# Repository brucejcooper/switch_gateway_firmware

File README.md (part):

# Switch Gateway Lighting System

A complete home lighting control system built around a **WIZnet W5100S-EVB-Pico
(RP2040)** as the central controller. The board owns all physical hardware,
controls lights in response to button presses, and talks to Home Assistant via
MQTT **directly over its on-board Ethernet** — no external bridge host.

> **On-board MQTT (current architecture).** The MQTT bridge that once ran as an
> external `mqtt_bridge.py` process on a USB-tethered host now runs **on-board on
> Pico core 1**, over the W5100S hardwired TCP/IP chip. The Python bridge has
> been **deleted** — it lives only in git history as a behavioural reference for
> the C reimplementation in `src/net/`. As a consequence the USB-CDC port is now
> a **human text CLI only**: it carries no JSON command/event stream.

---

## System Architecture

```
RS-485 bus @ 38400 baud (canonical; firmware auto-recovers slaves left at 19200 or 9600)

W5100S-EVB-Pico (RP2040) — Modbus master, single source of truth
 ├── core 0: Modbus master · button matrix (PIO) · button FSM · DALI world
 │           model · command queue · state cache · persistence · USB-CDC CLI
 ├── core 1: W5100S Ethernet · MQTT connection mgmt · Home Assistant
 │           discovery / availability / state ↔ command translation (JSON)
 │
 ├── Waveshare 32CH Relay Board (slave 1)   — 32 relay coils
 ├── TinyModbus DALI Gateway (slave 2)      — up to 64 ballasts
 ├── TinyModbus DALI Gateway (slave 3)      — up to 64 ballasts
 └── 24 switch fixtures × up to 7 buttons   — PIO matrix scan

   │ Ethernet (W5100S, on-board)              │ USB CDC (human text CLI only)
   ▼                                          ▼
 Mosquitto + Home Assistant            screen / picocom / miniterm
```

The two cores exchange **typed C structs** over two single-producer/single-
consumer queues (`intercore.c`) — **not JSON**. Core 0 forwards state events to
core 1 (`ic_event_t`); core 1 forwards translated commands back to core 0
(`ic_cmd_t`). JSON exists only at core 1's MQTT edge (`src/net/ha_bridge.c`).

### Key design principles

**The board is the master.** It owns the RS-485 bus and all lighting state. HA is
a client — if HA, the broker, or the network goes away, buttons and lights keep
working normally. A network outage never reboots the device: core 1 keeps looping
through its reconnect state machine while core 0 runs the lights. Core 0 only
feeds the hardware watchdog while core 1's heartbeat is fresh, so a genuine
core-1 wedge (not a network outage) is what triggers a reboot.

**State is never assumed.** Core 0 only updates its state cache from hardware
readback — DALI queries sent to the ballasts themselves — never from the
commands it sent. The gateway caches nothing, so the ballasts are the only
authority.
This correctly handles DALI min/max level clamping and ballast-side fade curves.

**Discovery is republished on every connect.** On each MQTT (re)connect core 1
re-publishes the full HA auto-discovery set and then requests a `resync`, so HA
repopulates from scratch. Broker and network settings live in `/config.json`
(set with the `mqtt` / `net` CLI commands, or HA's `lighting/config/...` topics);
friendly names and rooms are done in HA's device registry UI.

---

## Hardware

| Device | Role | Modbus Slave ID |
|--------|------|-----------------|
| Waveshare Modbus RTU Relay 32CH | Relay control — lights, fans, switches | 1 |
| TinyModbus ATtiny1604 DALI Gateway #1 | DALI bus A — up to 64 ballasts | 2 |
| TinyModbus ATtiny1604 DALI Gateway #2 | DALI bus B — up to 64 ballasts | 3 |
| WIZnet W5100S-EVB-Pico (RP2040) | Main controller, button scanner, Modbus master, on-board Ethernet/MQTT | — |

Function-code mappings and register addresses for the Waveshare board:
<https://www.waveshare.com/wiki/Modbus_RTU_Relay_32CH>.

### Pin assignments (W5100S-EVB-Pico, RP2040)

| Function | GPIO |
|----------|------|
| RS-485 UART TX | 4 |
| RS-485 UART RX | 5 |
| RS-485 DE (drive enable) | 1 |
| Button matrix SER | 6 |
| Button matrix CLK | 7 |
| Button matrix COL base (8 columns → GP8–GP15) | 8 |
| W5100S SPI0 SCK | 18 |
| W5100S SPI0 MOSI | 19 |
| W5100S SPI0 MISO | 16 |
| W5100S SPI0 CSn | 17 |
| W5100S RSTn | 20 |
| W5100S INTn | 21 |

SPI0 (GP16–21) is owned exclusively by core 1; the RS-485 UART and USB CDC are
owned by core 0. The button matrix tops out at GP15, leaving the SPI block clear.

### Baud rate setup

The canonical bus speed is **38400**. It was previously 19200, on the belief
that 38400 was marginal for the TinyModbus slaves' internal-RC oscillator; the
real cause was a tinyAVR silicon erratum in the USART start-of-frame detector,
and with that fixed both bauds measure a 0.00 % frame-error rate. 38400 cuts the
average transaction from 12.65 ms to 8.96 ms.

The firmware auto-recovers slaves left on another speed. On boot it pings each
slave at 38400, then walks 19200 (the old canonical speed) and 9600 (the factory
default) on timeout, sends the per-device set-baud command, and verifies the
slave came back at 38400 — all logged under the `disc` module tag.

| Slave kind | Set-baud register | Value (38400) |
|---|---|---|
| Waveshare 32CH Relay | FC06 `0x2000` | `0x0003` |
| TinyModbus DALI gateway | FC06 `0x1F03` | `0x0002` |

The set-baud writes are persisted on the slaves, so the fallback path only
fires once per device. After the first successful boot, subsequent boots
take <100 ms total for all three slaves.

If a slave is unreachable at 38400, 19200 and 9600 alike, the discovery logs
`E disc: slave N (...) unreachable at both bauds` and boot continues
without that slave — the relay sync / DALI scan will see it as missing.
Most commonly this means the slave is unplugged, has a different baud
rate (e.g. left at 38400 from an earlier config), or is at a different slave
address than configured. Manual recovery is easy from the CLI: `ping <slave>`
to probe, `discover` to re-run auto-recovery across all configured slaves, or
`set_slave_baud <slave> {9600|19200|38400}` to push a baud at a known rate.
The slave-address writes for factory-fresh devices (TinyModbus FC06 `0x1F02`
value `0x0002` or `0x0003`; Waveshare FC06 `0x4000` value `0x0001`) are
one-time and must be done manually before the first boot.

---

## Firmware

### Building

Requires the Pico SDK, pico-vfs, ioLibrary_Driver and coreMQTT (all git
submodules — `git submodule update --init --recursive`). The board is selected
in `CMakeLists.txt` (`PICO_BOARD wiznet_w5100s_evb_pico`), which targets the
RP2040 and pins the W5100S SPI defaults — a Pico 2 / RP2350 UF2 will not boot
this board.

```bash
mkdir build && cd build
cmake ..
make -j$(nproc)
```

`FW_VERSION` is built from git on every build: `<base>+<git describe --tags
--always --dirty>` (e.g. `2.0.0+791ca0b-dirty`), via `cmake/gen_version.cmake`
→ `build/generated/version.h`. The base (`2.0.0`) lives in `CMakeLists.txt`.

Flash `light_switch.uf2` with picotool. For example:

```bash
build % make && picotool load -f -x light_switch.uf2 && sleep 2 && pyserial-miniterm /dev/tty.usbmodem112201
```

### Boot Sequence

Each boot, before the main loop starts, the firmware runs:

1. **stdio + alarm pool init**, then a ~2.5 s USB-enumeration settle.
2. **Core 1 launched early** (`core1_launch()`), *before* `fs_init()`. Core 1
   registers as the flash-lockout victim (`flash_safe_execute_core_init`), which
   the first-boot littlefs format requires, then **parks** until core 0 hands it
   a config snapshot — it does not bring up the network yet.
3. **Filesystem init** — pico-vfs / littlefs mount/format.
4. **Config + mapping load** — `/config.json` and `/mappings.json` (defaults if
   absent; legacy files auto-migrated, see [Persistent Storage](#persistent-storage)).
5. **State cache init** — zeros the in-memory entity state.
6. **Modbus init** — UART at the persisted baud rate (38400 default).
7. **Bus discovery** — for each configured slave, ping at 38400, fall back to
   9600, auto-reconfigure if needed (see "Baud rate setup" above).
8. **DALI interrogation ARMED** — for each gateway, arm a full DALI
   interrogation and carry on. It is *not* waited on: the main loop drives it,
   state fills in over the next few hundred ms per ballast, and
   `dirty_poll_tick()` emits scan-complete when it finishes. Boot reaches the
   main loop in ~3.5 s regardless of how much gear is on the bus, or whether a
   configured gateway is absent (which can never finish a scan at all).
9. **Relay full sync** — read all 32 coils on the Waveshare board into the state
   cache, queue relay state events.
10. **Button + serial init** — PIO scanner, USB-CDC text CLI.
11. **Config snapshot handed to core 1** (`intercore_set_snapshot` +
    `core1_config_ready()`): slave lists + MQTT broker/creds + network settings.
    Core 1 now brings up the W5100S, DHCP/static IP, and the MQTT connection
    manager, and on connect publishes the full HA discovery set.
12. **Watchdog enabled** — 5 s timeout, plus a core-1 launch grace window. Only
    after this point are stalls fatal. Discovery and scans run unwatchdog'd
    because they can take seconds in failure paths.

### Source file overview

| File | Purpose |
|------|---------|
| `main.c` | Startup, init sequence, core-1 launch, main loop, watchdog feed |
| `modbus.c/h` | Modbus RTU master — ISR-driven, non-blocking |
| `bus_discovery.c/h` | Boot-time slave ping + auto baud recovery |
| `button_actions.c/h` | PIO button matrix scanner |
| `button_fsm.c/h` | Per-button state machine (toggle/dim/reversal) |
| `button_fsm_emit.c` | Pushes typed button events to core 1 |
| `config.c/h` | Global config, persisted to `/config.json` (timing, slaves, modbus baud, MQTT, net) |
| `mapping.c/h` | Button-to-light mappings, persisted to `/mappings.json` |
| `state_cache.c/h` | In-memory cache of relay + DALI ballast + group state |
| `lighting_actions.c/h` | Command dispatch, any-on probe + config-query state machines, state event queue |
| `dali_queue.c/h` | DALI adapter: per-slave priority scheduler + producer API over the generic client |
| `dali_pending.c/h` | Latest-wins desired-state table per gateway (64 ballast + 16 group slots) that absorbs HA/web/CLI bursts |
| `mbq_client.c/h` | Generic DALI-agnostic command-queue client (queue protocol v4, one FC 0x41 per transaction) |
| `dali_state.c/h` | the DALI world model: presence, level/status, groups, fade tracking |
| `dali_commission.c/h` | controller-side IEC 62386-102 commissioning |
| `dirty_poll.c/h` | relay-board polling + gateway sysinfo/reachability |
| `cli.c/h` | USB-CDC text CLI (verb table, line editing, `show`/`dali`/`cfg`/...) |
| `ic_seam.c/h` | The core-0/core-1 inter-core seam — g_config's single writer + event forwarding |
| `cli_provision.c/h` | Provision status → core-1 event forwarding |
| `dali_provision.c/h` | DALI commissioning state machine |
| `intercore.c/h` | The two typed SPSC queues + the config snapshot |
| `core1.c/h` | Core-1 entry point, heartbeat, flash-lockout victim |
| `net/netif.c/h` | W5100S bring-up / DHCP / link recovery state machine |
| `net/wizchip_glue.c/h` | SPI/CS/reset glue for the WIZnet ioLibrary |
| `net/mqtt_app.c/h` | coreMQTT connection manager (connect, LWT, sub/pub, TX flow) |
| `net/ha_bridge.c/h` | HA auto-discovery, availability, event↔MQTT translation |
| `log.c/h` | Logging facility (LOG_INFO/WARN/ERR/DBG macros) emitting to USB CDC |

### Main loop (core 0)

```c
while (true) {
    modbus_poll();               // advance Modbus state machine (ISR-driven, non-blocking)
    wd_feed();                   // feed watchdog iff core 1's heartbeat is fresh
    lighting_any_on_probe_tick();// submit any-on probe queries into the gateway queue
    lighting_cfg_query_tick();   // submit config queries into the gateway queue
    dq_tick();                   // drive the gateway command queue (FC 0x41 enqueue+ack)
    button_fsm_tick();           // classify raw button events, dispatch commands
    dali_state_tick();           // interrogate ballasts: verify, discover, sweep
    dirty_poll_tick();           // relay board + gateway sysinfo
    dali_provision_tick();       // advance commissioning state machine if active
    cli_poll();                  // read text CLI input, dispatch commands
    ic_seam_pump();              // drain core-1 cmds; forward state events to core 1
    wd_feed();
}
```

Core 0 is cooperative — no blocking calls in normal operation. Core 1 runs its own
loop (`netif_tick → mqtt_app_tick → ha_bridge_tick`) on the second core.

---

## Button Behaviour

Each of the 24 switch fixtures can have up to 7 physical buttons. Each button
can control multiple lights simultaneously (all mapped lights mirror each other).

### Gesture recognition

| Gesture | Action |
|---------|--------|
| Short press (< 500 ms) | Toggle all mapped lights on/off |
| Hold (≥ 500 ms) | Start dimming: down if any light is on, up if all are off |
| Release while dimming | Stop. Light settles at current level |
| Re-press within 400 ms of release | Reverse direction, continue dimming |
| Re-press after 400 ms | Treated as a new short press |

Dimming uses DALI Up/Down commands at the ballast's own fade rate, issued
at 200 ms intervals (5 steps/second). The actual brightness change per step
is controlled by the ballast hardware.

### Timing defaults (configurable via the `cfg` CLI command or `lighting/config/<field>/set`)

| Parameter | Default | Description |
|-----------|---------|-------------|
| `long_press_ms` | 500 ms | Hold threshold before dimming begins |
| `dim_repeat_ms` | 200 ms | Interval between DALI Up/Down commands |
| `reversal_window_ms` | 400 ms | Window after release to trigger direction reversal |
| `gw_diag_interval_ms` | 30000 ms | How often each DALI gateway's sysinfo (uptime/reboots/reset reason) is polled and published to HA; 0 disables |

### Button events sent to HA

Every button gesture is also published to HA as an event entity, so HA
automations can react to button presses independently of the built-in mapping.

Physical `press`/`release` frame every interaction; the gesture events
(`click`, `long_press`, `long_press_repeat`) overlay them. A **tap** emits
`press` then `click` + `release`; a **hold** emits `press`, `long_press`,
`long_press_repeat`…, `release`.

| Event type | When fired |
|------------|------------|
| `press` | Physical button down (every interaction) |
| `release` | Physical button up (every interaction) |
| `click` | A completed short tap (down→up before the long-press threshold) |
| `long_press` | Hold threshold crossed (also fires on direction reversal) |
| `long_press_repeat` | Each dim-rate tick while held (~5 Hz) |

---

## Lighting State Tracking

### Relay channels

A wall button sends its coil write (FC05) at once. HA, web and CLI commands set
the channel's **desired state** instead; `lighting_relay_tick()` drains those
with one FC05 write in flight at a time (see
[Bursts](#bursts-latest-wins-desired-state)). Either way the cache and HA are
updated from the write ACK, never from the request. Relay state is
instantaneous — no polling needed after a command.

The Waveshare board's state is also read in full at boot to synchronise the
cache with the hardware's actual state (handles Pico restarts while power was on).

### DALI ballasts — the controller's world model (`dali_state.c`)

**The controller learns the bus by asking the ballasts.** Task 05 removed every
gateway cache, so presence, arc level, status and group membership are all
established by DALI queries sent through the command queue — nothing is read
from a gateway register any more.

Three sources of work, in priority order, at most one query in flight per slave:

1. **Post-command verification** (`DQ_PRIO_LEVEL_READ`). Any command marks what
   it touched — one ballast, a group's cached members, or everything for a
   broadcast — and the toucher is re-read immediately so user-visible state
   converges without waiting for a sweep.
2. **Discovery** (`DQ_PRIO_BACKGROUND`). A full pass over all 64 addresses:
   `QUERY STATUS` → `QUERY ACTUAL LEVEL` → `QUERY GROUPS 0-7` → `QUERY GROUPS
   8-15`. Run at boot, by CLI `scan`, and after provisioning. It is **not**
   paced by the sweep interval — measured at **4.87 s** for 64 addresses,
   because an absent address costs a single query.
3. **Background sweep** (`DQ_PRIO_BACKGROUND`). One ballast per
   `dali_sweep_interval_ms` (default 10 s, 0 = off; tunable from the CLI, HA and
   the web UI). This is a *backstop* for
   what nothing tells us about — a ballast that lost power, or gear changed
   outside this controller — not the mechanism. Every 6th step probes an
   **absent** address instead, so gear that was off at boot or added later is
   discovered without a manual scan.

**Fade tracking.** A DAPC lands immediately but the level *ramps*, so a single
read taken mid-fade would cache a value on the way to the destination. The
verifier re-reads while `QUERY STATUS` bit 4 (FADE RUNNING) is set, at 250 ms,
until it settles — bounded at 95 s (past DALI's longest fade) so a stuck fade
bit cannot pin the bus.

**Presence — absence needs proof.** Only a CLEAN no-answer to a directed query
counts against presence, and normally only after two consecutive. A collision,
bus fault or dropped command is evidence about the **bus**, not the ballast, so
it freezes the counters and keeps the current belief. The one exception: an
**explicit scan is authoritative** and drops presence on the first clean
no-answer — a scan is a deliberate re-establishment of ground truth (boot,
`scan`, post-provisioning) and is precisely when addresses are expected to have
moved. Without that, every address vacated by a re-provision lingered as a
phantom in HA, one per sweep step.

The controller never caches an arc level from the command it sent — it reads
back what actually happened. That is what makes DALI min/max clamping report
honestly (commanded 128 on a binary relay ballast → reports 254 with status
`0x0C`, limit error), rather than the controller claiming a level the gear never
reached.

#### TinyModbus register contract

The gateway caches nothing about the bus. It serves a DALI command queue and its
own diagnostics; every value the controller reports comes from a DALI query it
issued and got an answer to.

- **DALI command queue** — the only path for level changes, group/broadcast and
  specialty sends, and all raw queries. One user-defined function code, **FC
  0x41**, carries all of it: a request optionally enqueues one command and
  optionally acks the head of the gateway's response queue, and the reply reports
  the fate of the enqueue plus the current head. No register block is involved,
  and the retired FC23 ranges (`0x1000`/`0x1010`) now answer ILLEGAL DATA
  ADDRESS. See "DALI command queue: adapter + generic client" below,
  [`../TinyModbus/QUEUE-PROTOCOL.md`](../TinyModbus/QUEUE-PROTOCOL.md) for the
  normative contract, and `../TinyModbus/README.md`. The CLI `dali_raw` /
  `read_mem` go through the queue via `dq_submit_sync`.
- **Per-ballast config** is controller-owned: it **reads** each field with raw
  DALI queries (the config-query state machine in `lighting_actions.c`, routed
  through the command queue) and **writes** it with a DTR0+SET pair submitted as
  one queue command. Controller and gateway are a **matched firmware set** —
  deploy both together.
- **Group membership** is read with `QUERY GROUPS` and written with
  `ADD/REMOVE FROM GROUP` frames; commissioning runs in `dali_commission.c`.
  The action registers are slave-addr `0x1F02`, baud `0x1F03` and system-reset
  `0x1F05`.
- **Gateway recovery:** `0x1F05` (write `0xA5A5`) software-resets a wedged
  gateway (CLI `gw_reboot`). RX error counters live at FC04 `0x0300`; uptime /
  boot-count / reset-reason at FC04 `0x0310` (read `get_input <slave> 0x0310 4`
  — a reboot shows as uptime dropping or boot-count incrementing); the queue's
  own counters at FC04 `0x0320` (CLI `mbq gw <slave>`). Every FC04 block is an
  **exact-length** read — a different count returns ILLEGAL DATA ADDRESS rather
  than a short read.

The canonical specification for the gateway is
[`../TinyModbus/README.md`](../TinyModbus/README.md).

### Absent slaves are backed off

A slave that is not there costs `MODBUS_MAX_RETRIES`+1 attempts × the 50 ms
response timeout — ~186 ms of bus per transaction, every time any producer polls
it. That was measured as the **largest single contributor to worst-case command
latency**: a Modbus transaction cannot be preempted, so a button press arriving
behind one waits it out.

After three consecutive dead transactions the transport stops putting that slave
on the wire. Requests to it complete immediately as a timeout without
transmitting, so producers see exactly what they saw before, minus the bus cost.
Backoff doubles 1 s → 60 s; one **single-attempt** probe is allowed through each
time it expires (a probe only asks "are you back?", and the retries are what make
it expensive); any valid reply — including a Modbus exception, which is the slave
alive and disagreeing — clears it at once.

Two producer-side companions, because a skipped request completes *instantly* and
every producer's pacing assumes a transaction costs ~25 ms of wall time: the
world model stops generating sweep work for a down gateway, and `mbq_client`
backs a silent slave off exponentially, 5 ms doubling to a 1 s ceiling (spec §5,
"dead-slave backoff"). Without those the bus was spared but the main loop
churned — ~12 000 pointless requests in 76 s. A *refusal* (slave in backoff,
action queue full) returns instantly and needs the same gate as a timeout: one
bench reboot drill spun 8785 transactions at 1.6 ms apiece against a 50 ms wire
timeout before the backoff covered both.

Measured, idle bus: worst case **236 ms → 89 ms**, with *two* absent slaves
configured rather than the one that produced the 236. `busload` reports the
backed-off slave count and skipped-transaction count.

### Scheduler model

The queue client is fed by a **pull scheduler**, not a shared backlog. Storage is
partitioned by priority class, and each class carries **its own gateway depth**:

| class | storage | in-flight depth | what uses it |
|---|---|---|---|
| provisioning | 2 | **1** | the commissioning sequence (each step depends on the previous answer) |
| user | 8 | 3 | wall buttons, toggle probes — sized to one button's full fan-out |
| desired state | 80 slots + 16 membership lists, latest-wins | **2** | HA / web / HTTP API / CLI on-off-level and group-membership edits — a table, not a FIFO; see [Bursts](#bursts-latest-wins-desired-state) |
| config | 3 | 3 | DTR0+SET config writes |
| verification read | 4 | 3 | the re-read that carries a command's real outcome to HA |
| background | 2 | **2** | the world-model sweep, config-query rotation |

Depth matters because the **gateway executes strictly FIFO with no priority** —
anything already submitted delays a button by a whole DALI frame. The gateway's
own queue is only `CMDQ_DEPTH` = **2** deep (one executing, one next), so the
ladder's remaining lever is keeping background out of the second slot: capped at
2 of the scheduler's 3, background can never put a button press behind two DALI
frames. Measured at the older 8-slot depth, background load cost a user command
**+13 ms median** against **+75 ms** for the same load admitted at user depth.

**`DQ_INFLIGHT_MAX` is `CMDQ_DEPTH + 1` = 3, and the extra one is not extra
queue.** It is the command that rides the same transaction which collects the
oldest result. Without it that collection needs a transaction of its own —
measured 2.04 Modbus transactions per DALI frame on the first v4 bench run,
worse than the FC23 path v4 replaced. Real gateway occupancy is still capped at
2 by the client itself, so the scheduler cannot overfill the gateway; the +1
only stops it starving the pipeline.

While a slave is provisioning the scheduler ships **only** the provisioning
class, so nothing can interleave with the binary search — a stray DTR0 write
mid-bisect would corrupt it.

**Dim steps are counters, not commands.** A held button emits repeats faster than
DALI can issue them, so queueing each step makes the light keep dimming after
release. `dq_add_delta()` accumulates a signed per-ballast/per-group step count
which the scheduler drains one frame per submit opportunity, rotating across
targets for fairness. Real UP/DOWN frames still go out — the ballast's own fade
rate and min/max clamping govern the result, deliberately not a DAPC computed
from cache. The counter decrements on **submit** and saturates at ±4: losing a
step to the clamp or a gateway reboot is invisible in a ramp, whereas replaying
one would double-step.

### Bursts: latest-wins desired state

**HA commands are not queued as frames.** Siri's "turn off all the lights" is
~65 separate `light.turn_off` calls arriving within a few ms (HomeKit has no
"all"), and scenes can be bigger. Dispatched one frame each into the 8-deep user
class, everything past the eighth was dropped. Measured 2026-10-10 on the house
with a 107-command burst (61 ballasts, 14 groups, 32 relays, published in 11 ms):
**57 of 75 DALI commands and 7 of 32 relays lost**, nothing reported to HA, and a
wall press in the following ~200 ms was itself refused (`backlog full`) or took
276 ms. The intercore queue lost nothing — core 0 empties it every pass.

Every such command is **absolute**, so only the newest per target matters. Each
gateway keeps a pending table (`dali_pending.c`): one slot per short address and
per group, holding off / on (GOTO LAST ACTIVE) / level plus a write stamp. A new
command overwrites its slot; the table cannot overflow. The scheduler drains it
as a rung of the ladder — below the user class and dim steps, above config
writes, verification reads and background — at depth **2**: like background it
may keep the gateway full but never takes the staging slot, so a wall press
arriving mid-drain is staged next and waits only for the frames already at the
gateway. **Buttons always win.** Measured on the house (2.0.1+8bc2861) with a
USER-class `dali_raw` fired 0–200 ms behind a 206-command burst: **94–157 ms**,
never refused (idle: 40 ms) — against `backlog full` at +0/+100 ms and 276 ms at
+200 ms before. Same burst: 0 drops at every stage, 45 relay writes for 64
commands, each DALI target shipped once.

**Group vs member: oldest-written ships first, and that is all.** A ballast's
final level is set by whichever of its own slot and its groups' slots executes
last; in stamp order that is the one written most recently — exactly what a FIFO
that never overflowed would produce. "group 3.15 OFF, then 3.4 ON" leaves 3.4 on;
"group OFF" written again afterwards moves the group to newest and everything
ends off. No membership lookup is involved, so a stale membership cache cannot
make it wrong (`test/dali_pending_test.c` checks this against a model bus over
thousands of random streams).

**Buttons vs pending state.** A press skips the table, so an older pending slot
could otherwise execute after it and undo it (Siri's group OFF still draining
when someone hits the switch). After a press ships, its own pending slot is
dropped — or, if anything else is still pending on that gateway, the press is
re-asserted as the **newest** slot, so nothing older can land after it. That
costs one idempotent frame, only during a drain. A dim step drops its target's
pending slot (a step is relative, so there is nothing to re-assert). If the user
class ever refuses a press, the press goes into the table rather than being lost.

**Group membership edits don't block either.** They used to submit each ADD/REMOVE
TO GROUP frame into the user class and spin the bus (up to 2 s per frame) until
there was room, so replacing a big group stalled core 0 for about a second. Now
each group has a pending add list and remove list in the same table, latest wins
per (ballast, group) pair, and the frames (send-twice, idempotent) drain in the
same write order as everything else, so "set G5's members, then G5 on" changes
the members first. An edit is diffed against the membership last *requested* as
well as the measured cache, because the cache lags a frame that has shipped but
not yet been read back; CLI `add=`/`remove=` start from the requested membership
for the same reason. Each frame's ballast is re-interrogated as it ships, so
`QUERY GROUPS` stays the only writer of the membership cache.

**Blocking CLI commands keep absorbing bursts.** `dali_raw`, `read_mem` and the
Modbus `get_*`/`set_*` verbs wait on the bus by design. While they do, the
wait loop moves queued HA light commands (set_dali / set_group / set_relay —
none of which can block) into the tables, stopping at the first command of any
other kind so nothing is reordered. Before this a 214-command burst lost 41
commands at the intercore queue behind one `dali_raw`.

**State stays measured.** Nothing writes the cache from a request. The
verification read is marked when a slot's frame actually ships, and since the
table outranks verification reads on a gateway that executes FIFO, the read can
never run before the command it verifies.

**Relays** get the same rule per channel, drained with one FC05 write in
flight at a time, so a burst can no longer overflow the Modbus action queue
(~8 ms per write: 32 relays drain in about a quarter of a second). **Not FC15:**
the Waveshare 32CH does not answer an FC15 over one 8-coil bank at all — silent
timeouts, then backoff — measured live 2026-10-10. A full 32-coil FC15 might
work, but the board returns FC01 reads byte-swapped (`relay_byteswap`) and its
FC15 data order is undocumented, so trying it risks switching the wrong relays.

Duplicate idempotent submits that have not shipped are folded, so a repeated
press or a re-published HA state costs nothing. A class-full refusal is
**backpressure**, not an error — a polling producer sees it routinely — so it is
a rate-limited counter (`refused=` in `dq`), not a warning per event.

### DALI command queue: adapter + generic client (`dali_queue.c` / `mbq_client.c`)

Every group/broadcast/specialty DALI send and every raw query goes through a
**two-layer** command queue:

1. **`mbq_client.c` — the generic, DALI-agnostic client.** It speaks **queue
   protocol v4**: one user-defined function code, **FC 0x41**, carries every
   transaction. A request optionally **enqueues** one opaque 4-byte command and
   optionally **acks** the head of the gateway's response queue; the reply
   reports the fate of the enqueue (an **accept byte** carrying a
   gateway-assigned sequence) and the current head. Results are **retained by
   the gateway until acked**, so no lost reply can destroy one. The client
   delivers a terminal outcome (`complete` / `failed` / `lost` /
   `result_lost`) + an 8-bit response per command, and knows nothing about
   DALI. The normative specification is
   [`../TinyModbus/QUEUE-PROTOCOL.md`](../TinyModbus/QUEUE-PROTOCOL.md) — §1
   wire formats, §4 recovery, §5 client policy, §6 diagnostics; the header
   comment in `src/mbq_client.h` is the controller-side summary of it.
2. **`dali_queue.c` — the DALI adapter** on top. It owns the per-slave priority
   scheduler and the producer API, packs a DALI command into the client's 4
   opaque command bytes, and maps the client's outcome back to a `dq_result_t`.

**Scheduler and priority ladder (the adapter).** Each gateway has a per-slave
**priority backlog** in front of the gateway's 2-deep command queue. Producers
(`dq_submit`) drop commands in with a **priority class**; `dq_tick()` ships the
highest-priority pending command first (FIFO within a class), applying that
class's own depth (see [Scheduler model](#scheduler-model) above). A command
carries an **idempotency** flag that decides what happens to it if a reboot or a
never-landed frame catches it. The ladder, highest first: **provisioning**
(bus-exclusive — while a slave is being commissioned the scheduler admits
nothing else on it) → **user actions** (wall-button on/off, the any-on probe)
→ **dim steps** → **desired state** (HA/web/CLI on/off/level and
group-membership edits, latest-wins — see
[Bursts](#bursts-latest-wins-desired-state)) → **config writes** (DTR0+SET) →
**verification reads** → **background** (the world-model sweep, config
rotation).

**Sequences belong to the gateway.** Sequences run 1–31 (0 = "none") and are
assigned **exclusively** by the gateway; the master never proposes one, it
learns each command's identity from the accept byte. That is what makes a
gateway reboot self-correcting — the counter restarts and the master simply
learns the new numbers. There is **no id ledger** (v1's controller-assigned id
sequence with a result ring, credit tracking and a boot_count-driven
resync/rebuild/rollback machine) and **no optimistic slot mirror** (v2's 8-slot
lifecycle, where a locally predicted slot state could mis-attribute a status).
Both were the source of the recovery-corruption bugs those generations kept
re-fixing, and neither exists to go wrong here.

**One transaction per DALI frame — and the pacing that buys it.** In steady
state a single transaction acks the previous result, collects the next, and
enqueues one command. That property is **conditional on the client pacing
itself**: whenever it has no enqueue it is allowed to send, it schedules the
next transaction for the estimated completion of its oldest in-flight command
rather than polling to find out. A client that polls whenever it cannot enqueue
measures **2.04 transactions per command** — worse than the FC23 design v4
replaces. A correct client issues essentially no polls at all in steady state
(measured: 814 enqueues against 2 polls over 400 pairs). A poll is for recovery
and for a genuinely overdue result, never for asking whether the gateway is
done yet.

**Recovery is rules R1–R4, and there is no fallback path.** The client's whole
reconcile logic is spec §4:

| rule | observation | conclusion |
|---|---|---|
| **R1** | reply to an enqueue+ack lost; the recovery poll shows the head no longer holding the acked seq | the ack applied — and since ack and enqueue travel in **one** frame, that proves the whole frame landed. Bind the command to the predicted seq, resend nothing |
| **R1′** | same, but the head still holds the acked seq | the frame never arrived. Resend it verbatim, ack included |
| **R2** | an accept byte returns a seq the master still tracks | the gateway restarted its counter — a live seq cannot recur without a reboot |
| **R3** | the head holds a seq the master is not tracking | rebooted; an unknown seq has no other source |
| **R4** | a result deadline expires with no result | poll, then classify against the gateway's sysinfo `boot_count` (FC04 `0x0310`, cold path) |

Three details of that are load-bearing. The branches are evaluated in a
**defined order** on a recovery poll, because R1/R1′ and R3 can look at the same
observation and disagree. An **empty head is ambiguous** — "the ack applied and
the queue happened to drain" and "a reboot wiped the queue" are
indistinguishable from the head alone — and is resolved by a cold-path
`boot_count` read on a path that is already exceptional. And the predicted seq
is a prediction that gets **verified**: when the result surfaces its seq must
match, and a mismatch is a counted, logged fault (`pred_faults` in `mbq`), never
silently accepted.

**A blocked head is not a missing result, and R4 must not confuse the two.** A
result deadline has a third cause besides loss and a wedge: the gateway's own
backpressure rule. While the head still holds a result the master has consumed
but failed to ack, everything behind it is invisible and the gateway
deliberately stalls its DALI arbiter rather than dropping anything. Letting the
deadline expire there would have R4 resend a command the gateway is still
holding — a **double execution of a real DALI frame, reported to nobody**, and
it was reproduced on the bench. So while the head is known-blocked the client
pushes its deadlines out and lets them run again once the head moves. Those
episodes are counted (`head_blocked` in `mbq_stats_t`); they climb during the
`no-ack` drill and should be zero otherwise.

Before a slave's first accept byte there is **no baseline** and the client does
not pretend otherwise: prediction is unavailable, so a lost reply to that first
enqueue resolves conservatively (idempotent resends, non-idempotent disposed
`lost`), and a head bearing an untracked seq is swallowed as a leftover from the
previous controller epoch rather than read as a reboot. On its own reboot the
client **drains, waits one result deadline, and drains again** before submitting
anything — a command accepted before the controller died is still executing, and
its result would otherwise land after the first drain and fire R3 against a
gateway that never rebooted.

**Payload contract (the adapter).** A DALI command packs into the 4 opaque bytes
as `[addr, data, flags, dtr0]`, where `flags` is `DQ_TWICE` / `DQ_DTR0` /
`DQ_ANSWER` — these are aliases for `MBQ_QF_*`, which are the **wire bits** in
their wire positions, so nothing translates between the producer and the frame.
On completion the client's 8-bit response is the DALI backward-frame answer (on
`complete`) or a failure code (`NAK` / `collision` / `bus fault`, on `failed`),
which the adapter maps to `DQ_RES_OK` / `DQ_RES_NAK` / `DQ_RES_ERR`. The
**collision-vs-NAK** distinction is preserved for the any-on probe (a garbled
backward frame → `DQ_RES_ERR` → "≥1 on"; silence → `DQ_RES_NAK` → "none on").

**Four result classes, and the fourth matters.** `MBQ_R_COMPLETE`,
`MBQ_R_FAILED`, `MBQ_R_LOST` and **`MBQ_R_RESULT_LOST`**. The last one means the
command **ran** and its answer died with the gateway's response queue — the bus
state changed, so a caller that would retry on `LOST` must **not** retry on
this. A gateway reboot that discards a non-idempotent command still surfaces to
the producer as `DQ_RES_DROPPED`; idempotent ones (GOTO_LAST_ACTIVE, group
on/off/level, config re-store, all queries) are resubmitted by the client, while
UP/DOWN step frames never are.

**Client policy (spec §5), as implemented here.** Single outstanding transaction
per slave — the prediction rule and R1 both depend on it. Round-robin across
slaves with work pending, which is the adapter's job and bounds any slave's wait
to one transaction time per competing slave. In-flight cap = `CMDQ_DEPTH` (**2**,
`mbq_client.h`), which **must match the gateway's `CMDQ_DEPTH` in
`TinyModbus/src/cq.h`** — nothing on the wire carries the depth, so a bump
applied to one side only ships silently. The ack is **always piggybacked**, which
is what keeps R1 available. Enqueue frames are **never auto-retried by the
transport** (a timeout goes to §4; poll/ack-only frames may retry freely, since
re-acking a popped seq is a no-op). Failures are delivered verbatim, with retry
policy belonging to the scheduler's priority classes rather than the transport.

**Matched firmware set, latched at discovery.** Controller and gateway are a
matched pair with no negotiation and no fallback, so the client reads the
gateway's version string (FC04 `0x0200`) at discovery and **refuses, loudly and
per slave, to drive a non-matching queue generation** rather than limping: major
version ≥ 1 is queue v4, 0.x is pre-v4. A behavioural latch backs it up — an
ILLEGAL FUNCTION for FC 0x41, or a reply whose length the request never called
for — so a gateway that reports a version it does not actually speak is still
caught. An incompatible slave is disabled and flagged in `mbq`.

**Bench drill knobs (permanent instrumentation, not scaffolding).** Two CLI
switches force the real §4 paths against real hardware instead of simulating
them:

- **`mbq drop-reply <slave> <n>`** discards the next `n` replies inside the
  client, *after* transport accounting and *before* resolution. Dropping the
  reply to an enqueue+ack exercises R1/R1′; dropping the reply to an ack-less
  first enqueue exercises the deadline and the `boot_count` corner.
- **`mbq no-ack <slave> <n>`** withholds the piggybacked ack on the next `n`
  requests, so the gateway's response queue fills and its backpressure rule
  stalls the DALI arbiter rather than dropping a result. Nothing is lost;
  resuming acks drains it and the rate recovers.

**Observability.** **`dq [slave]`** dumps the per-class pending counts and
depths, the pending dim deltas and cursor, the in-flight count, the
desired-state table (`desired: N pending, written / overwritten / shipped /
button / member_ops` — overwritten is how much a burst coalesced, button how
often a press cleared or re-asserted a slot, member_ops the membership frames
requested), and its counters
(submitted / ok / nak / err / dropped / refused / coalesced / steps / clamped),
then the client's own dump. **`mbq [slave]`** is that dump on its own: per-slave
FSM state, the current ack/head/last-seq binding, estimated response-queue
occupancy, each tracked command's state and seq, and the §6 counters —
transactions split enqueue / poll / recovery-poll, timeouts, `A_FULL`, resends,
R1 vs R1′ outcomes, deadlines, `boot_count` reads, **reboots split by which rule
noticed them** (R2 / R3 / R4 — a fleet that only ever notices reboots via R4
deadlines is one whose structural rules are not firing, which is itself the
finding), the fault counters (`predicted-seq`, `orphans`, `protocol` — all three
should read 0 forever), the four result classes, and round-trip timing.
**`mbq gw <slave>`** reads the gateway's own queue counters (FC04 `0x0320`,
exactly 8 registers): `accepts, a_full, executes, results, acks, stalls,
q_discard, spare`. Two of those look alarming and are not — **`a_full` non-zero is
the saturation signal**, meaning the gateway's queue is full and its DALI engine
fully fed (the client re-offers immediately; ~72 % of transactions are refusals
under load, and that share is the headroom gauge), while **`stalls` non-zero is
normal**, the backpressure rule doing its job. Bare `dq` /
`mbq` = all DALI slaves. For throughput and correctness under load, see
[`busload` and `soak`](#measuring-the-command-path-busload-and-soak).

**Subsystems on the queue.** Every former single-slot producer rides it: the raw
command path (button on/off/step, group commands, config DTR0+SET), the **any-on
probe**, the **config-query** state machine, and the blocking **CLI helpers**
(`dali_raw` / `read_mem`, via `dq_submit_sync`). The probe and the config queries
are ordinary expects-answer commands — no shared-result-register interlock, no
settle-gate. `read_mem`'s per-byte SET-DTR0 + READ is one atomic `DQ_DTR0` queue
entry. The click-grace guarantee holds: a probe query resolves in a couple of
round-trips (tens of ms), inside the button FSM's 150 ms grace; a rare overflow
lands on the pre-existing assume-off fallback, bounded by the 600 ms probe
deadline.

#### What v4 measured against the FC23 design it replaces

Bench figures, saturated, slave 3 at 19200 — historical, taken before 38400
became canonical and before the SFDEN erratum fix:

| | FC23 | v4 |
|---|---|---|
| RS-485 occupancy, saturated | 99 % | **37 %** |
| Modbus transactions per DALI command | 1.73 | **1.03** |
| throughput (DTR0 write/read pairs) | 14.71/s | ~13.9–14.1/s |
| endurance | — | 5000 pairs / 10 000 frames, 0 bad, 0 failures of 20 748 transactions |

Throughput is flat because the DALI bus, not Modbus, is the limit — the win is
that the bus is now two-thirds idle at the same rate, which is what makes a
second DALI gateway workable.

**A gateway reboot mid-traffic is handled cleanly**: across a six-run drill,
zero mis-attributed results, zero stale reads, zero out-of-order deliveries. One
query per reboot is reported `RESULT_LOST` — it was executing when the gateway
restarted, so its answer genuinely no longer exists. Reporting that honestly is
the designed behaviour, not a defect.

### State event flow to HA

```
Hardware change
  → dali_state_tick() interrogates the ballast (QUERY STATUS / ACTUAL LEVEL)
     — from a post-command verification mark, or the background sweep
  → lighting_emit_dali_state() pushes levt_t to the core-0 event ring
  → ic_seam_pump() drains the ring, converts to a typed ic_event_t
  → intercore_push_event() — onto the core-0 → core-1 SPSC queue
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
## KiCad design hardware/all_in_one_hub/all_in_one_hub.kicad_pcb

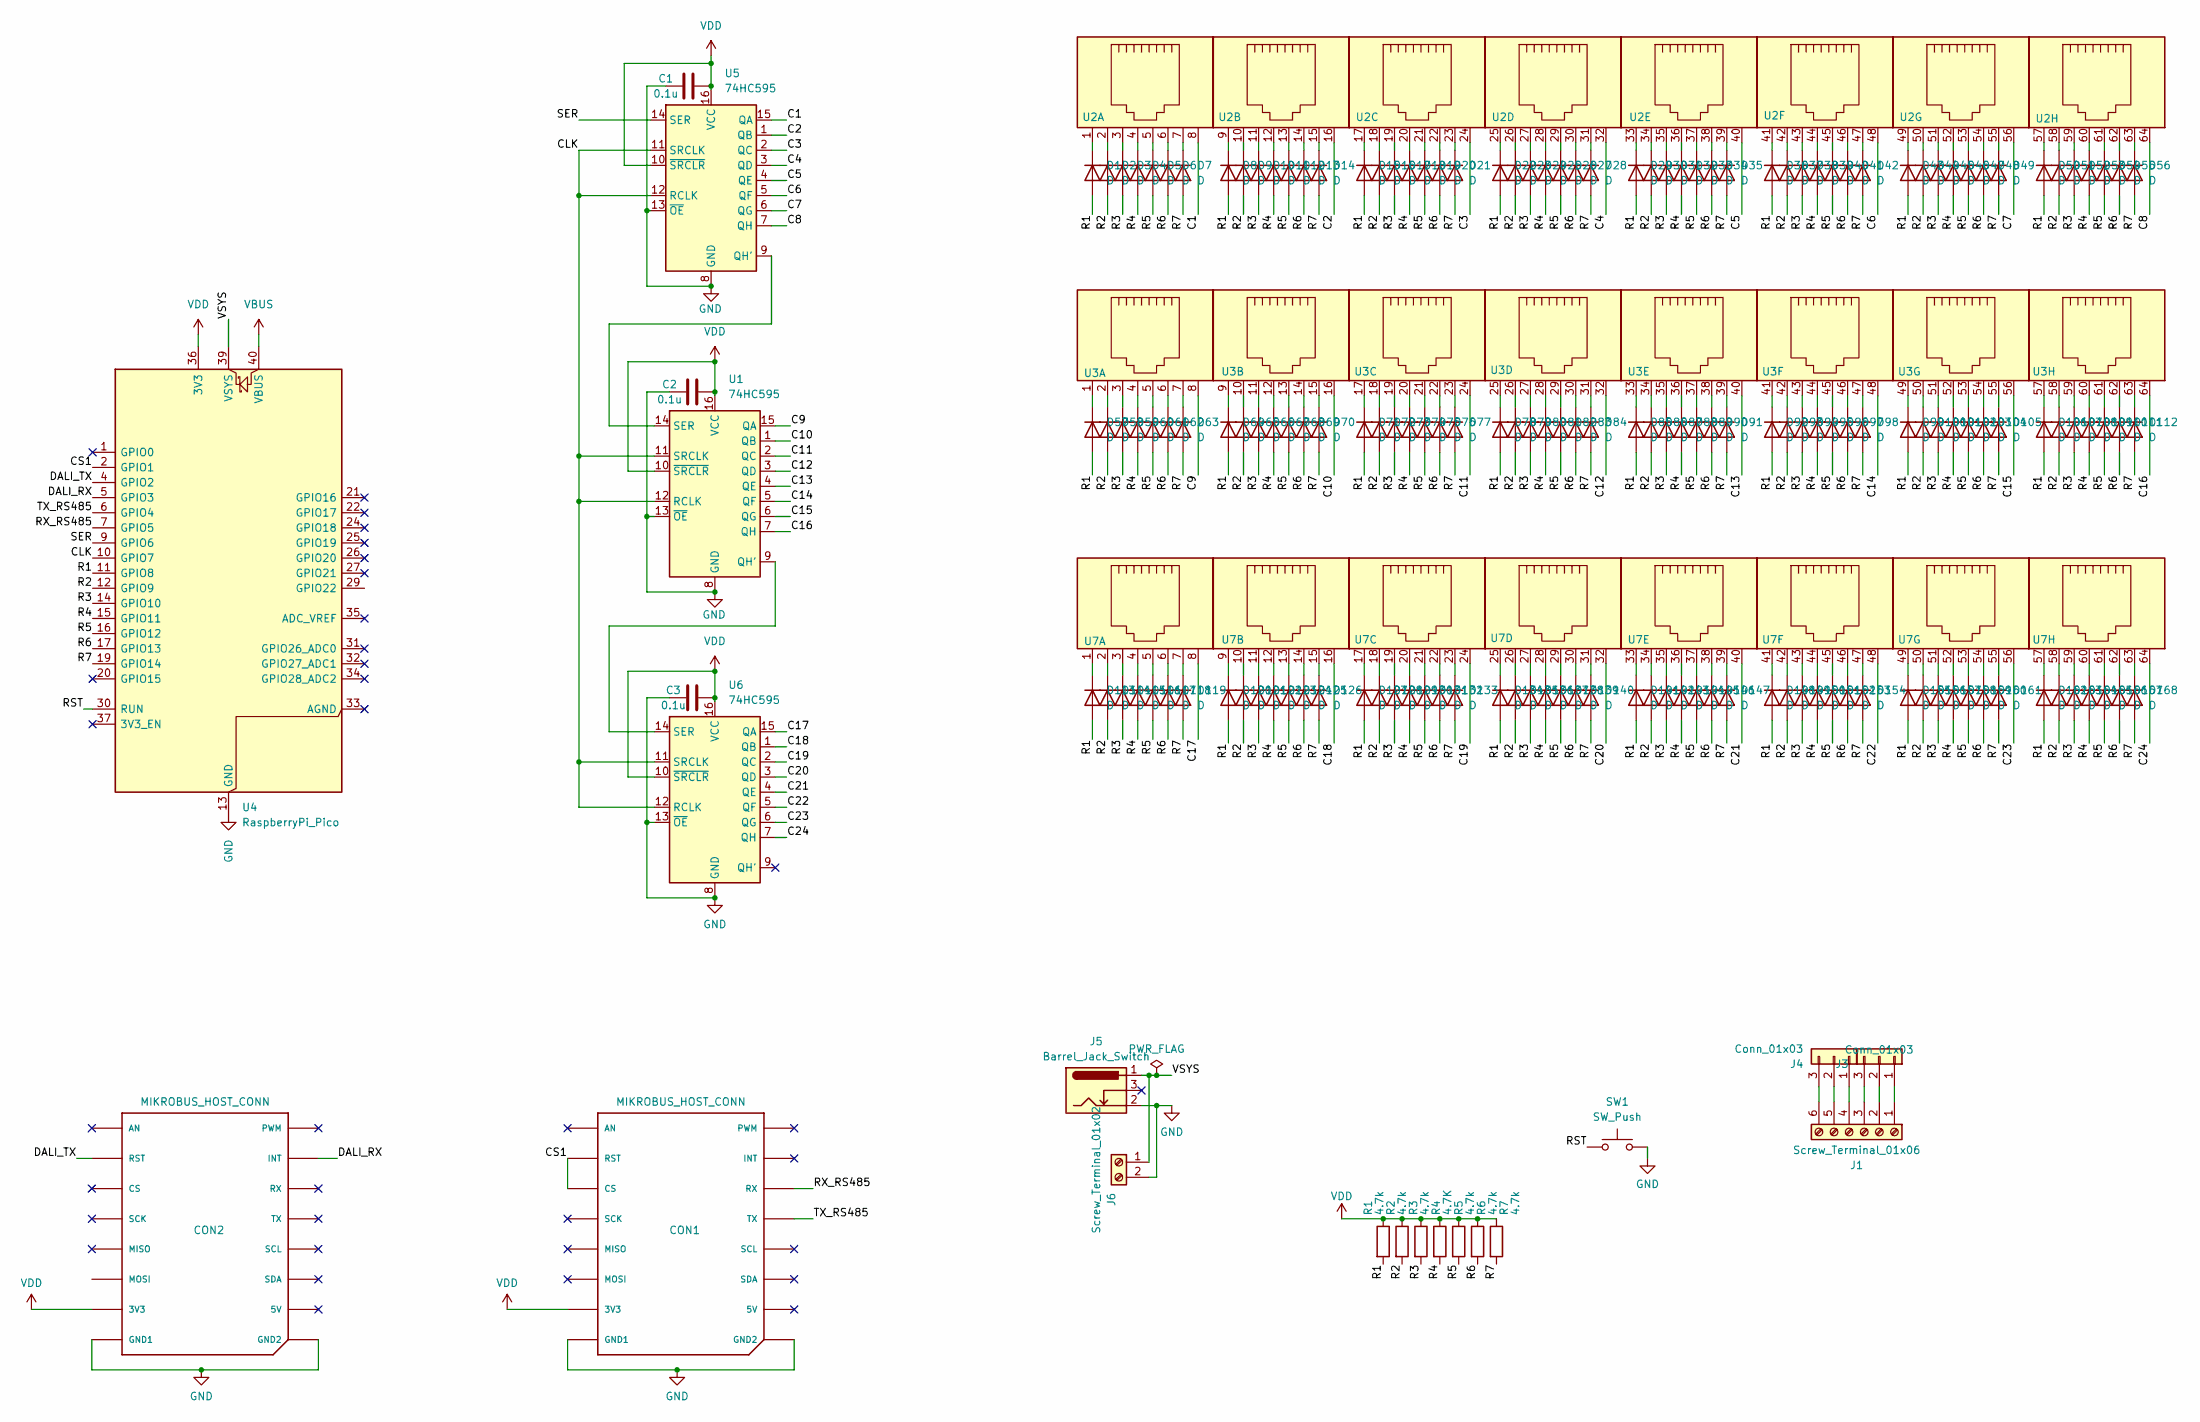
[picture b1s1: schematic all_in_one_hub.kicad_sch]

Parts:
C1, C2, C3: 0.1u; C_0805_2012Metric
CON1, CON2: MIKROBUS_HOST_CONN
D1, D2, D3, D4, D5, D6, D7, D8, D9, D10, D11, D12, D13, D14, D15, D16, D17, D18, D19, D20, D21, D22, D23, D24, D25, D26, D27, D28, D29, D30, D31, D32, D33, D34, D35, D36, D37, D38, D39, D40, D41, D42, D43, D44, D45, D46, D47, D48, D49, D50, D51, D52, D53, D54, D55, D56, D57, D58, D59, D60, D61, D62, D63, D64, D65, D66, D67, D68, D69, D70, D71, D72, D73, D74, D75, D76, D77, D78, D79, D80, D81, D82, D83, D84, D85, D86, D87, D88, D89, D90, D91, D92, D93, D94, D95, D96, D97, D98, D99, D100, D101, D102, D103, D104, D105, D106, D107, D108, D109, D110, D111, D112, D113, D114, D115, D116, D117, D118, D119, D120, D121, D122, D123, D124, D125, D126, D127, D128, D129, D130, D131, D132, D133, D134, D135, D136, D137, D138, D139, D140, D141, D142, D143, D144, D145, D146, D147, D148, D149, D150, D151, D152, D153, D154, D155, D156, D157, D158, D159, D160, D161, D162, D163, D164, D165, D166, D167, D168: D; D_SOD-123F
J1: Screw_Terminal_01x06; TerminalBlock_Phoenix_MKDS-1,5-6-5.08_1x06_P5.08mm_Horizont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
J3, J4: Conn_01x03; PinHeader_1x03_P2.54mm_Vertical
J5: Barrel_Jack_Switch; BarrelJack_Horizontal
J6: Screw_Terminal_01x02; TerminalBlock_Phoenix_MKDS-1,5-2-5.08_1x02_P5.08mm_Horizont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
R1, R2, R3, R5, R6, R7: 4.7k; R_0603_1608Metric
R4: 4.7K; R_0603_1608Metric
SW1: SW_Push; SW_Tactile_SKHH_Angled
U1, U5, U6: 74HC595; SOIC-16_3.9x9.9mm_P1.27mm
U2, U3, U7: Molex 8pc*8pole RJ45
U4: RaspberryPi_Pico; RaspberryPi_Pico_Common

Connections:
/C1: U2.8, U5.15 (QA)
/C2: U2.16, U5.1 (QB)
/C3: U2.24, U5.2 (QC)
/C4: U2.32, U5.3 (QD)
/C5: U2.40, U5.4 (QE)
/C6: U2.48, U5.5 (QF)
/C7: U2.56, U5.6 (QG)
/C8: U2.64, U5.7 (QH)
/C9: U1.15 (QA), U3.8
/C10: U1.1 (QB), U3.16
/C11: U1.2 (QC), U3.24
/C12: U1.3 (QD), U3.32
/C13: U1.4 (QE), U3.40
/C14: U1.5 (QF), U3.48
/C15: U1.6 (QG), U3.56
/C16: U1.7 (QH), U3.64
/C17: U6.15 (QA), U7.8
/C18: U6.1 (QB), U7.16
/C19: U6.2 (QC), U7.24
/C20: U6.3 (QD), U7.32
/C21: U6.4 (QE), U7.40
/C22: U6.5 (QF), U7.48
/C23: U6.6 (QG), U7.56
/C24: U6.7 (QH), U7.64
/CLK: U1.11 (SRCLK), U1.12 (RCLK), U4.10 (GPIO7), U5.11 (SRCLK), U5.12 (RCLK), U6.11 (SRCLK), U6.12 (RCLK)
/CS1: CON1.P2 (RST), CON1.P3 (CS), U4.2 (GPIO1)
/DALI_RX: CON2.P15 (INT), U4.5 (GPIO3)
/DALI_TX: CON2.P2 (RST), U4.4 (GPIO2)
/R1: D1.2 (A), D8.2 (A), D15.2 (A), D22.2 (A), D29.2 (A), D36.2 (A), D43.2 (A), D50.2 (A), D57.2 (A), D64.2 (A), D71.2 (A), D78.2 (A), D85.2 (A), D92.2 (A), D99.2 (A), D106.2 (A), D113.2 (A), D120.2 (A), D127.2 (A), D134.2 (A), D141.2 (A), D148.2 (A), D155.2 (A), D162.2 (A), R1.2, U4.11 (GPIO8)
/R2: D2.2 (A), D9.2 (A), D16.2 (A), D23.2 (A), D30.2 (A), D37.2 (A), D44.2 (A), D51.2 (A), D58.2 (A), D65.2 (A), D72.2 (A), D79.2 (A), D86.2 (A), D93.2 (A), D100.2 (A), D107.2 (A), D114.2 (A), D121.2 (A), D128.2 (A), D135.2 (A), D142.2 (A), D149.2 (A), D156.2 (A), D163.2 (A), R2.2, U4.12 (GPIO9)
/R3: D3.2 (A), D10.2 (A), D17.2 (A), D24.2 (A), D31.2 (A), D38.2 (A), D45.2 (A), D52.2 (A), D59.2 (A), D66.2 (A), D73.2 (A), D80.2 (A), D87.2 (A), D94.2 (A), D101.2 (A), D108.2 (A), D115.2 (A), D122.2 (A), D129.2 (A), D136.2 (A), D143.2 (A), D150.2 (A), D157.2 (A), D164.2 (A), R3.2, U4.14 (GPIO10)
/R4: D4.2 (A), D11.2 (A), D18.2 (A), D25.2 (A), D32.2 (A), D39.2 (A), D46.2 (A), D53.2 (A), D60.2 (A), D67.2 (A), D74.2 (A), D81.2 (A), D88.2 (A), D95.2 (A), D102.2 (A), D109.2 (A), D116.2 (A), D123.2 (A), D130.2 (A), D137.2 (A), D144.2 (A), D151.2 (A), D158.2 (A), D165.2 (A), R4.2, U4.15 (GPIO11)
/R5: D5.2 (A), D12.2 (A), D19.2 (A), D26.2 (A), D33.2 (A), D40.2 (A), D47.2 (A), D54.2 (A), D61.2 (A), D68.2 (A), D75.2 (A), D82.2 (A), D89.2 (A), D96.2 (A), D103.2 (A), D110.2 (A), D117.2 (A), D124.2 (A), D131.2 (A), D138.2 (A), D145.2 (A), D152.2 (A), D159.2 (A), D166.2 (A), R5.2, U4.16 (GPIO12)
/R6: D6.2 (A), D13.2 (A), D20.2 (A), D27.2 (A), D34.2 (A), D41.2 (A), D48.2 (A), D55.2 (A), D62.2 (A), D69.2 (A), D76.2 (A), D83.2 (A), D90.2 (A), D97.2 (A), D104.2 (A), D111.2 (A), D118.2 (A), D125.2 (A), D132.2 (A), D139.2 (A), D146.2 (A), D153.2 (A), D160.2 (A), D167.2 (A), R6.2, U4.17 (GPIO13)
/R7: D7.2 (A), D14.2 (A), D21.2 (A), D28.2 (A), D35.2 (A), D42.2 (A), D49.2 (A), D56.2 (A), D63.2 (A), D70.2 (A), D77.2 (A), D84.2 (A), D91.2 (A), D98.2 (A), D105.2 (A), D112.2 (A), D119.2 (A), D126.2 (A), D133.2 (A), D140.2 (A), D147.2 (A), D154.2 (A), D161.2 (A), D168.2 (A), R7.2, U4.19 (GPIO14)
/RST: SW1.1, U4.30 (RUN)
/RX_RS485: CON1.P14 (RX), U4.7 (GPIO5)
/SER: U4.9 (GPIO6), U5.14 (SER)
/TX_RS485: CON1.P13 (TX), U4.6 (GPIO4)
/VSYS: J5.1, J6.1, U4.39 (VSYS)
GND: C1.1, C2.1, C3.1, CON1.P8 (GND1), CON1.P9 (GND2), CON2.P8 (GND1), CON2.P9 (GND2), J5.2, J6.2, SW1.2, U1.8 (GND), U1.13 (~OE), U4.3 (GND), U4.8 (GND), U4.13 (GND), U4.18 (GND), U4.23 (GND), U4.28 (GND), U4.38 (GND), U5.8 (GND), U5.13 (~OE), U6.8 (GND), U6.13 (~OE)
unnamed: D1.1 (K), U2.1
unnamed: D2.1 (K), U2.2
unnamed: D3.1 (K), U2.3
unnamed: D4.1 (K), U2.4
unnamed: D5.1 (K), U2.5
unnamed: D6.1 (K), U2.6
unnamed: D7.1 (K), U2.7
unnamed: D8.1 (K), U2.9
unnamed: D9.1 (K), U2.10
unnamed: D10.1 (K), U2.11
unnamed: D11.1 (K), U2.12
unnamed: D12.1 (K), U2.13
unnamed: D13.1 (K), U2.14
unnamed: D14.1 (K), U2.15
unnamed: D15.1 (K), U2.17
unnamed: D16.1 (K), U2.18
unnamed: D17.1 (K), U2.19
unnamed: D18.1 (K), U2.20
unnamed: D19.1 (K), U2.21
unnamed: D20.1 (K), U2.22
unnamed: D21.1 (K), U2.23
unnamed: D22.1 (K), U2.25
unnamed: D23.1 (K), U2.26
unnamed: D24.1 (K), U2.27
unnamed: D25.1 (K), U2.28
unnamed: D26.1 (K), U2.29
unnamed: D27.1 (K), U2.30
unnamed: D28.1 (K), U2.31
unnamed: D29.1 (K), U2.33
unnamed: D30.1 (K), U2.34
unnamed: D31.1 (K), U2.35
unnamed: D32.1 (K), U2.36
unnamed: D33.1 (K), U2.37
unnamed: D34.1 (K), U2.38
unnamed: D35.1 (K), U2.39
unnamed: D36.1 (K), U2.41
unnamed: D37.1 (K), U2.42
unnamed: D38.1 (K), U2.43
unnamed: D39.1 (K), U2.44
unnamed: D40.1 (K), U2.45
unnamed: D41.1 (K), U2.46
unnamed: D42.1 (K), U2.47
unnamed: D43.1 (K), U2.49
unnamed: D44.1 (K), U2.50
unnamed: D45.1 (K), U2.51
unnamed: D46.1 (K), U2.52
unnamed: D47.1 (K), U2.53
unnamed: D48.1 (K), U2.54
unnamed: D49.1 (K), U2.55
unnamed: D50.1 (K), U2.57
unnamed: D51.1 (K), U2.58
unnamed: D52.1 (K), U2.59
unnamed: D53.1 (K), U2.60
unnamed: D54.1 (K), U2.61
unnamed: D55.1 (K), U2.62
unnamed: D56.1 (K), U2.63
unnamed: D57.1 (K), U3.1
unnamed: D58.1 (K), U3.2
unnamed: D59.1 (K), U3.3
unnamed: D60.1 (K), U3.4
unnamed: D61.1 (K), U3.5
unnamed: D62.1 (K), U3.6
unnamed: D63.1 (K), U3.7
unnamed: D64.1 (K), U3.9
unnamed: D65.1 (K), U3.10
unnamed: D66.1 (K), U3.11
unnamed: D67.1 (K), U3.12
unnamed: D68.1 (K), U3.13
unnamed: D69.1 (K), U3.14
unnamed: D70.1 (K), U3.15
unnamed: D71.1 (K), U3.17
unnamed: D72.1 (K), U3.18
unnamed: D73.1 (K), U3.19
unnamed: D74.1 (K), U3.20
unnamed: D75.1 (K), U3.21
unnamed: D76.1 (K), U3.22
unnamed: D77.1 (K), U3.23
unnamed: D78.1 (K), U3.25
unnamed: D79.1 (K), U3.26
unnamed: D80.1 (K), U3.27
unnamed: D81.1 (K), U3.28
unnamed: D82.1 (K), U3.29
unnamed: D83.1 (K), U3.30
unnamed: D84.1 (K), U3.31
unnamed: D85.1 (K), U3.33
unnamed: D86.1 (K), U3.34
unnamed: D87.1 (K), U3.35
unnamed: D88.1 (K), U3.36
unnamed: D89.1 (K), U3.37
unnamed: D90.1 (K), U3.38
unnamed: D91.1 (K), U3.39
unnamed: D92.1 (K), U3.41
unnamed: D93.1 (K), U3.42
unnamed: D94.1 (K), U3.43
unnamed: D95.1 (K), U3.44
unnamed: D96.1 (K), U3.45
unnamed: D97.1 (K), U3.46
unnamed: D98.1 (K), U3.47
unnamed: D99.1 (K), U3.49
unnamed: D100.1 (K), U3.50
unnamed: D101.1 (K), U3.51
unnamed: D102.1 (K), U3.52
unnamed: D103.1 (K), U3.53
unnamed: D104.1 (K), U3.54
unnamed: D105.1 (K), U3.55
unnamed: D106.1 (K), U3.57
unnamed: D107.1 (K), U3.58
unnamed: D108.1 (K), U3.59
unnamed: D109.1 (K), U3.60
unnamed: D110.1 (K), U3.61
unnamed: D111.1 (K), U3.62
unnamed: D112.1 (K), U3.63
unnamed: D113.1 (K), U7.1
unnamed: D114.1 (K), U7.2
unnamed: D115.1 (K), U7.3
unnamed: D116.1 (K), U7.4
unnamed: D117.1 (K), U7.5
unnamed: D118.1 (K), U7.6
unnamed: D119.1 (K), U7.7
unnamed: D120.1 (K), U7.9
unnamed: D121.1 (K), U7.10
unnamed: D122.1 (K), U7.11
unnamed: D123.1 (K), U7.12
unnamed: D124.1 (K), U7.13
unnamed: D125.1 (K), U7.14
unnamed: D126.1 (K), U7.15
unnamed: D127.1 (K), U7.17
unnamed: D128.1 (K), U7.18
unnamed: D129.1 (K), U7.19
unnamed: D130.1 (K), U7.20
unnamed: D131.1 (K), U7.21
unnamed: D132.1 (K), U7.22
unnamed: D133.1 (K), U7.23
unnamed: D134.1 (K), U7.25
unnamed: D135.1 (K), U7.26
unnamed: D136.1 (K), U7.27
unnamed: D137.1 (K), U7.28
unnamed: D138.1 (K), U7.29
unnamed: D139.1 (K), U7.30
unnamed: D140.1 (K), U7.31
unnamed: D141.1 (K), U7.33
unnamed: D142.1 (K), U7.34
unnamed: D143.1 (K), U7.35
unnamed: D144.1 (K), U7.36
unnamed: D145.1 (K), U7.37
unnamed: D146.1 (K), U7.38
unnamed: D147.1 (K), U7.39
unnamed: D148.1 (K), U7.41
unnamed: D149.1 (K), U7.42
unnamed: D150.1 (K), U7.43
unnamed: D151.1 (K), U7.44
unnamed: D152.1 (K), U7.45
unnamed: D153.1 (K), U7.46
unnamed: D154.1 (K), U7.47
unnamed: D155.1 (K), U7.49
unnamed: D156.1 (K), U7.50
unnamed: D157.1 (K), U7.51
unnamed: D158.1 (K), U7.52
unnamed: D159.1 (K), U7.53
unnamed: D160.1 (K), U7.54
unnamed: D161.1 (K), U7.55
unnamed: D162.1 (K), U7.57
unnamed: D163.1 (K), U7.58
unnamed: D164.1 (K), U7.59
unnamed: D165.1 (K), U7.60
unnamed: D166.1 (K), U7.61
unnamed: D167.1 (K), U7.62
unnamed: D168.1 (K), U7.63
unnamed: J1.1, J3.1
unnamed: J1.2, J3.2
unnamed: J1.3, J3.3
unnamed: J1.4, J4.1
unnamed: J1.5, J4.2
unnamed: J1.6, J4.3
unnamed: U1.9 (QH'), U6.14 (SER)
unnamed: U1.14 (SER), U5.9 (QH')
VBUS: U4.40 (VBUS)
VDD: C1.2, C2.2, C3.2, CON1.P7 (3V3), CON2.P7 (3V3), R1.1, R2.1, R3.1, R4.1, R5.1, R6.1, R7.1, U1.10 (~SRCLR), U1.16 (VCC), U4.36 (3V3), U5.10 (~SRCLR), U5.16 (VCC), U6.10 (~SRCLR), U6.16 (VCC)

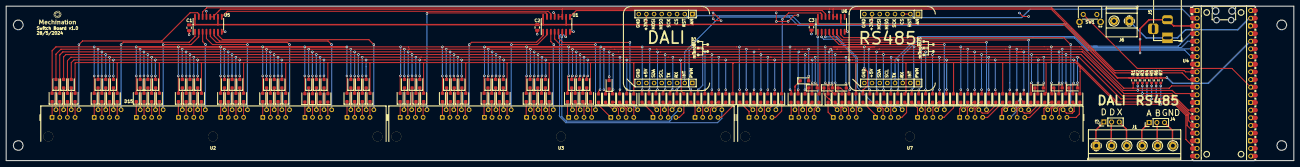
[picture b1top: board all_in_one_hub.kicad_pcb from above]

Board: 2 copper layers, 427.0 x 51.2 mm, 193 parts (0 on the bottom side), 218 nets.

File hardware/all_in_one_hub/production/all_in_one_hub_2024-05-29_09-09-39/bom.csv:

Designator,Footprint,Quantity,Value,LCSC Part #
"C1, C2, C3",805,3,0.1u,C49678
"D1, D10, D100, D101, D102, D103, D104, D105, D106, D107, D108, D109, D11, D110, D111, D112, D113, D114, D115, D116, D117, D118, D119, D12, D120, D121, D122, D123, D124, D125, D126, D127, D128, D129, D13, D130, D131, D132, D133, D134, D135, D136, D137, D138, D139, D14, D140, D141, D142, D143, D144, D145, D146, D147, D148, D149, D15, D150, D151, D152, D153, D154, D155, D156, D157, D158, D159, D16, D160, D161, D162, D163, D164, D165, D166, D167, D168, D17, D18, D19, D2, D20, D21, D22, D23, D24, D25, D26, D27, D28, D29, D3, D30, D31, D32, D33, D34, D35, D36, D37, D38, D39, D4, D40, D41, D42, D43, D44, D45, D46, D47, D48, D49, D5, D50, D51, D52, D53, D54, D55, D56, D57, D58, D59, D6, D60, D61, D62, D63, D64, D65, D66, D67, D68, D69, D7, D70, D71, D72, D73, D74, D75, D76, D77, D78, D79, D8, D80, D81, D82, D83, D84, D85, D86, D87, D88, D89, D9, D90, D91, D92, D93, D94, D95, D96, D97, D98, D99",D_SOD-123F,168,D,C64898
"R1, R2, R3, R4, R5, R6, R7",603,7,4.7k,C23162
"U1, U5, U6",SOIC-16_3.9x9.9mm_P1.27mm,3,74HC595,C10092

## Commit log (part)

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2025-11-12 Working C version
2025-11-12 added README
2025-11-17 Now we use LUA, and don't use FreeRTOS, because pico-vfs and FreeRTOS appear to be incompatible
2025-11-17 Removed cJSON as we aren't using it
2025-11-17 A few tweaks
2025-11-27 Fixing bugs
2025-12-29 Staging for moving to another machine
2026-01-23 Copeid values off old device
2026-02-01 Fixed typo with False and false
2026-03-08 Added binding helper functions
2026-03-13 Multi-button scripting
2026-03-13 Fixing typo
2026-03-13 fixing bugs in add function
2026-04-11 Fixed up provisioning, yet again
2026-04-19 Changed attribute setters to use DTR0 and send the command twice, as the spec requires
2026-04-27 vibe coded patch for new tinymodbus firmware and better ha
2026-04-27 added ha bridge
2026-04-27 removing unnecessary files
2026-05-15 Ready for mreging
2026-05-16 Updates for new TinyModbus
2026-05-16 Set up with some testing stuff for the new firmware
2026-05-16 added more debugs
2026-06-03 Debugged baud rate issues at 38400. It is now working reliably at 19200
2026-06-07 dirty_poll: drop invalid 0xFF level reads; add DALI wire-decode proof tool
    Belt-and-braces behind the gateway fix: if a brightness read ever comes back 0xFF
    (not a valid DALI level — max is 254), drop it and keep the last good value rather
    than reporting 100%.
    test/dali_wire_proof.py captures D0/D1 with the Saleae and Manchester-decodes the
    DALI forward+backward frames (self-validating against the known forward opcodes) so
    "what the ballast actually returned" is provable from the wire, not inferred.
2026-06-07 dirty_poll: only emit state_dali when the reportable state changes
    The gateway re-polls a fading ballast continuously (correct — until FADE_RUNNING
    clears), which made the controller emit an identical state_dali every ~100ms for the
    whole fade (e.g. 14x bri=99 fading=true when the target is the min). Now we emit only
    when arc level, the fading bit, or the lamp-fail bit changes; the cache is still
    updated and polling continues, so a real ramp still reports each step and the fade
    end (fading=false) is still reported — just no no-op spam.
2026-06-08 tools/xlsx_to_ha.py: migrate Switch wiring.xlsx into Home Assistant
    Reads the Lights + Switch Positions sheets and produces (then applies) a plan:
    - rename each DALI light device by (Device, Address) -> Light name; place at Map X/Y
    - rename each fixture (patch location L -> lighting_switch_plate_LL), set its
    button_order = the wiring string (order[position] = controller pin), place at
    Map X/Y; a patch location shared by two fixtures becomes one HA fixture with a
    split order "A+B" and a second (ext) marker placed from the 2nd fixture's Map X/Y
2026-06-08 relay availability: gate on relay-board reachability like DALI gateways
    Relays showed as available whenever the Pico was connected, even with the relay
    board absent — because the controller never polled the board for reachability and
    the bridge gated relay switches on the system topic only (DALI ballasts additionally
    gate on their gateway's state_gateway topic, which is why slave 3 went unavailable).
    Controller (dirty_poll.c): poll each relay slave's coils every 2s and emit
    state_gateway online/offline on a debounced transition, identical to the DALI
2026-06-11 Restoring Switch wiring
2026-06-13 Syncing, binding
2026-06-13 Ping
2026-06-14 Added some gitignores
